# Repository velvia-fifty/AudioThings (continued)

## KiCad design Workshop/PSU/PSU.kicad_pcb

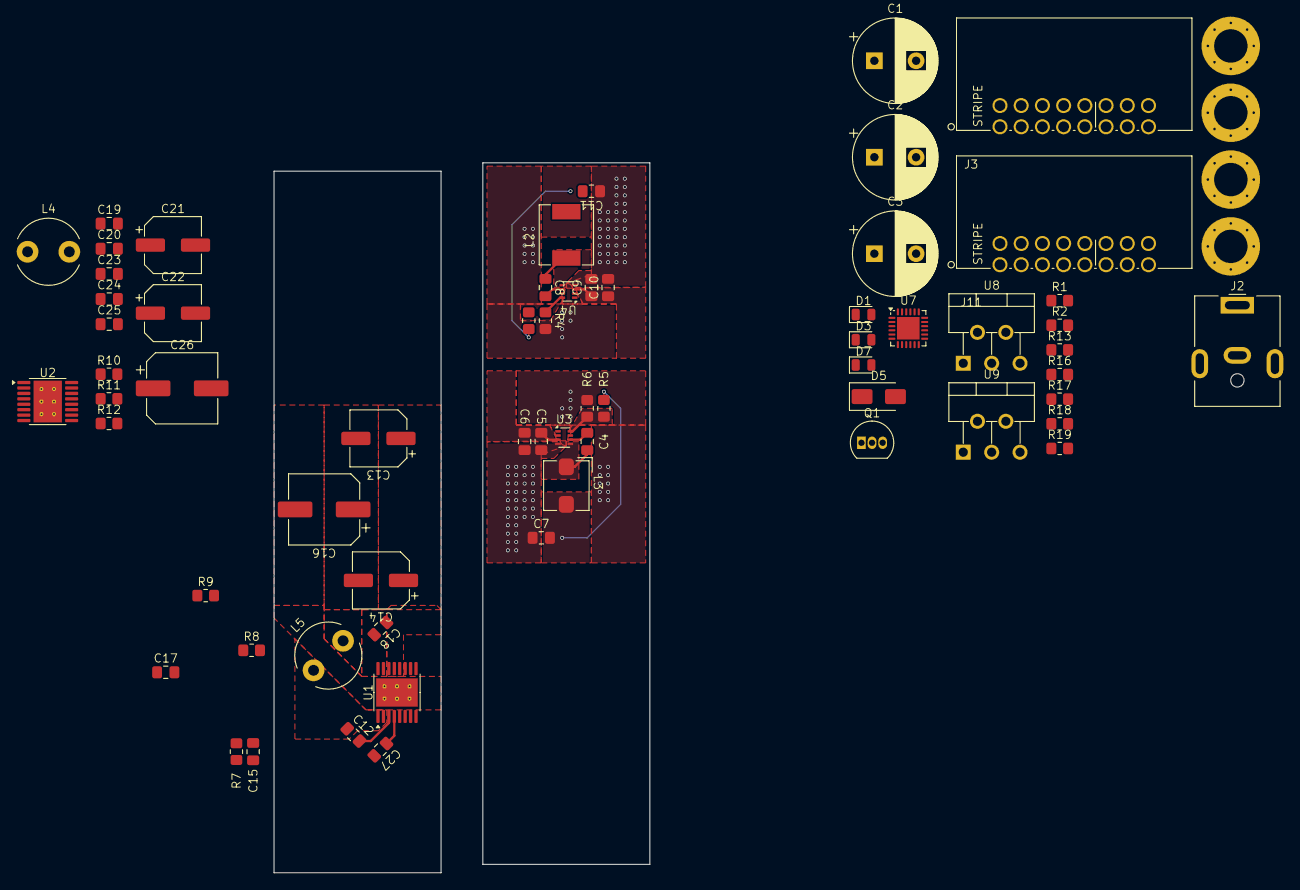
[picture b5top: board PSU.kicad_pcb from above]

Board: 2 copper layers, 45.0 x 85.0 mm, 67 parts (0 on the bottom side), 37 nets.

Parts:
C1, C3: 680uF; CP_Radial_D10.0mm_P5.00mm
C2: 180uF; CP_Radial_D10.0mm_P5.00mm
C4, C6, C8, C10: 100nF; C_0805_2012Metric_Pad1.18x1.45mm_HandSolder
C5, C9: 10uf; C_0805_2012Metric_Pad1.18x1.45mm_HandSolder
C7, C11: 47uf; C_0805_2012Metric_Pad1.18x1.45mm_HandSolder
C12, C23: 680nF; C_0805_2012Metric_Pad1.18x1.45mm_HandSolder
C13, C14, C21, C22: 56uF; CP_Elec_6.3x7.7
C15, C25: 150pF; C_0805_2012Metric_Pad1.18x1.45mm_HandSolder
C16, C26: 100uF; CP_Elec_8x6.9
C17, C18, C20, C24: 4.7uf; C_0805_2012Metric_Pad1.18x1.45mm_HandSolder
C19, C27: 2.2uf; C_0805_2012Metric_Pad1.18x1.45mm_HandSolder
D1: 5V OK; LED_0805_2012Metric
D3: -12V OK; LED_0805_2012Metric
D5: SMAZ18-13-F; D_SMA
D7: 12V OK; LED_0805_2012Metric
H1, H5, H6, H7: H_HOLE; H_ATX_PERF
J2: OPT_DC; BarrelJack_CUI_PJ-063AH_Horizontal
J3, J11: EURO_CONN; EURORACK Right Angle
L2: 5.6uH; IND_SRP6540-5R6M
L3: 4.7uH; L_Bourns_SRP5030T
L4, L5: 56uH; L_Radial_D7.8mm_P5.00mm_Fastron_07HCP
Q1: 2N3904; TO-92_Inline
R1, R2: 500; R_0805_2012Metric_Pad1.20x1.40mm_HandSolder
R3: 52k3; R_0805_2012Metric_Pad1.20x1.40mm_HandSolder
R4, R6, R17, R18: 10k; R_0805_2012Metric_Pad1.20x1.40mm_HandSolder
R5: 140k; R_0805_2012Metric_Pad1.20x1.40mm_HandSolder
R7, R11: 1M; R_0805_2012Metric_Pad1.20x1.40mm_HandSolder
R8, R10: 100k; R_0805_2012Metric_Pad1.20x1.40mm_HandSolder
R9, R12: 92k; R_0805_2012Metric_Pad1.20x1.40mm_HandSolder
R13: 150; R_0805_2012Metric_Pad1.20x1.40mm_HandSolder
R16: 1k; R_0805_2012Metric_Pad1.20x1.40mm_HandSolder
R19: 47k; R_0805_2012Metric_Pad1.20x1.40mm_HandSolder
U1, U2: LM43601PWPR; HTSSOP-16-1EP_4.4x5mm_P0.65mm_EP3.4x5mm_Mask2.46x2.31mm_The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
U3, U4: TPS563300; SOT-583-8
U7: STUSB4500QTR; QFN-24-1EP_4x4mm_P0.5mm_EP2.7x2.7mm
U8, U9: LM2596T-12; TO-220-5_P3.4x3.7mm_StaggerOdd_Lead3.8mm_Vertical

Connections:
+5V: D1.2 (A), J3.11, J3.12, J11.11, J11.12
+5v: C11.2, L2.2, R3.2
+12v: C2.1, C7.2, D7.2 (A), J3.9, J3.10, J11.9, J11.10, L3.2, R5.2, U8.4 (FB)
-12V: C3.2, D3.1 (K), J3.1, J3.2, J11.1, J11.2, Q1.1 (E), R18.1, U9.3 (GND)
-12v B: C16.2, C17.2, C18.2, C27.2, R9.2, U1.10 (AGND), U1.15 (PGND), U1.16 (PGND)
/5v FB: R3.1, R4.1, U4.8 (FB)
/5v SW: C8.1, L2.1, U4.5 (SW)
/12v FB: R5.1, R6.1, U3.8 (FB)
/12v SW: C4.1, L3.1, U3.5 (SW)
/+20V: C1.1, J2.1, U7.16 (VBUS_EN_SNK), U8.1 (VIN)
/-12v B Bias: C15.2, R7.2, R9.1, U1.9 (FB)
/-12v B CBOOT: C12.1, L5.1, U1.1 (SW), U1.2 (SW)
/CC1: U7.1 (CC1DB), U7.2 (CC1)
/CC2: U7.4 (CC2), U7.5 (CC2DB)
/CV: J3.13, J3.14, J11.13, J11.14
/GATE: J3.15, J3.16, J11.15, J11.16
/VBUS: R16.2, U7.24 (VDD)
COM: C1.2, C2.2, C5.2, C6.2, C7.1, C9.2, C10.2, C11.1, C13.2, C14.2, C15.1, C16.1, C17.1, C19.2, C20.2, C21.2, C22.2, C24.1, C24.2, C25.1, C25.2, C26.1, C26.2, H1.1, H5.1, H6.1, H7.1, J2.2, J3.3, J3.4, J3.5, J3.6, J3.7, J3.8, J11.3, J11.4, J11.5, J11.6, J11.7, J11.8, L4.2, L5.2, R1.1, R2.2, R4.2, R6.2, R7.1, R8.1, R10.1, R11.1, R11.2, R12.1, R12.2, U1.5 (BIAS), U2.5 (BIAS), U2.10 (AGND), U2.15 (PGND), U2.16 (PGND), U3.4 (GND), U4.4 (GND), U8.3 (GND), U8.5 (~ON/OFF)
unnamed: C23.1, L4.1, U2.1 (SW), U2.2 (SW)
unnamed: D1.1 (K), R13.2
unnamed: D3.2 (A), R2.1
unnamed: C3.1, R17.2, R19.2, U9.1 (VIN)
unnamed: D5.2 (A), Q1.2 (B), R18.2
unnamed: D5.1 (K), R17.1
unnamed: D7.1 (K), R1.2
unnamed: Q1.3 (C), R19.1, U9.5 (~ON/OFF)
unnamed: C12.2, U1.3 (CBOOT)
unnamed: R8.2, U1.8 (PGOOD)
unnamed: C27.1, U1.4 (VCC)
unnamed: C23.2, U2.3 (CBOOT)
unnamed: R10.2, U2.8 (PGOOD)
unnamed: C19.1, U2.4 (VCC)
unnamed: C4.2, U3.6 (BST)
unnamed: C8.2, U4.6 (BST)
unnamed: U7.10 (GND), U7.25 (GND)
unnamed: R16.1, U7.18 (VBUS_VS_DISCH)
PD +15v: C5.1, C6.1, C9.1, C10.1, C13.1, C14.1, C18.1, C20.1, C21.1, C22.1, U1.12 (EN), U1.13 (VIN), U1.14 (VIN), U2.12 (EN), U2.13 (VIN), U2.14 (VIN), U3.3 (VIN), U4.3 (VIN)

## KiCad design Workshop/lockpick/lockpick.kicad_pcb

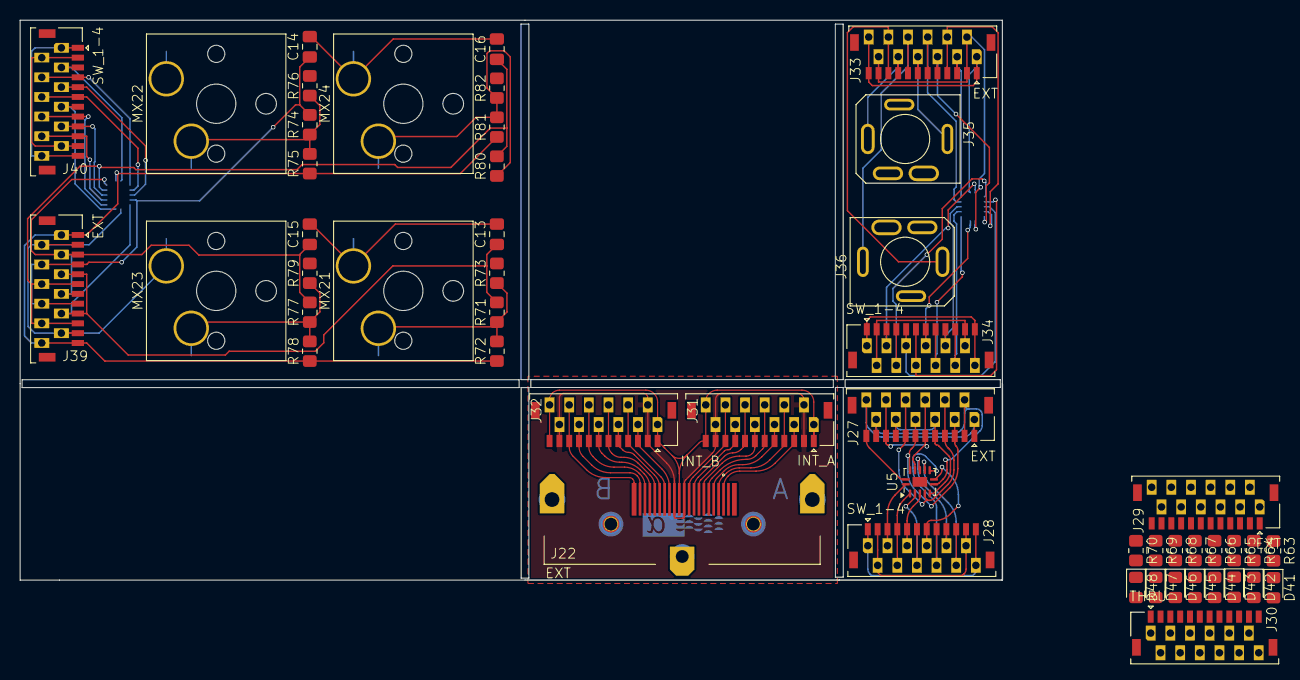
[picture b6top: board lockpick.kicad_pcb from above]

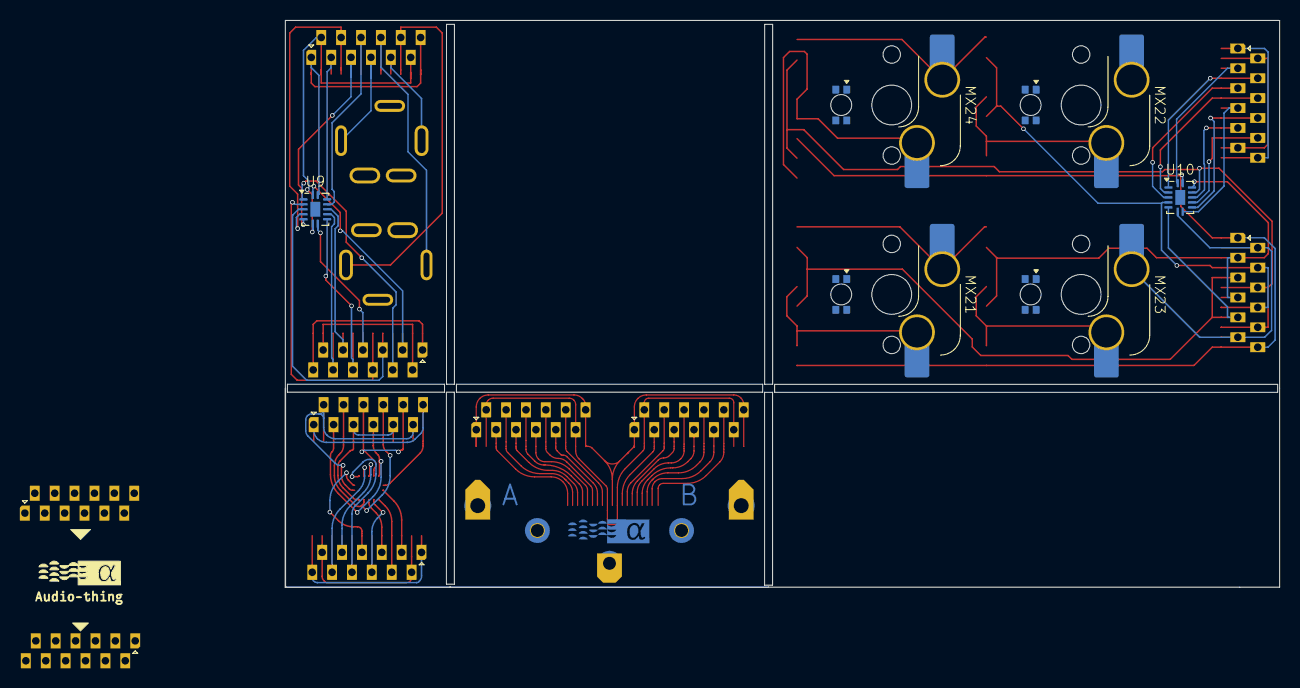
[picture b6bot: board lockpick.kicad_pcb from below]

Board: 2 copper layers, 100.0 x 57.0 mm, 53 parts (3 on the bottom side), 92 nets.

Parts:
***: at-logo-cu
C13, C14, C15, C16: 1uF; C_0805_2012Metric_Pad1.18x1.45mm_HandSolder
D41: ACT_1; LED_0805_2012Metric_Pad1.15x1.40mm_HandSolder
D42: ACT_2; LED_0805_2012Metric_Pad1.15x1.40mm_HandSolder
D43: ACT_3; LED_0805_2012Metric_Pad1.15x1.40mm_HandSolder
D44: ACT_4; LED_0805_2012Metric_Pad1.15x1.40mm_HandSolder
D45: ACT_5; LED_0805_2012Metric_Pad1.15x1.40mm_HandSolder
D46: ACT_6; LED_0805_2012Metric_Pad1.15x1.40mm_HandSolder
D47: ACT_7; LED_0805_2012Metric_Pad1.15x1.40mm_HandSolder
D48: ACT_8; LED_0805_2012Metric_Pad1.15x1.40mm_HandSolder
J22: EXT; AMPHENOL_10078837-001LF
J27, J29, J33, J39: EXT; JST_SHL 12pin w pads
J28, J34, J40: SW_1-4; JST_SHL 12pin w pads
J30: THRU; JST_SHL 12pin w pads
J31: INT_A; JST_SHL 12pin w pads
J32: INT_B; JST_SHL 12pin w pads
J35: MONO 1; SJ3-3505
J36: MONO 2; SJ3-3505
MX21: Trigger 3; SW_Hotswap_Kailh_MX_Plated_1206R LED
MX22: Trigger 2; SW_Hotswap_Kailh_MX_Plated_1206R LED
MX23: Trigger 1; SW_Hotswap_Kailh_MX_Plated_1206R LED
MX24: Trigger 4; SW_Hotswap_Kailh_MX_Plated_1206R LED
R63, R64, R65, R66, R67, R68, R69, R70, R73, R76, R79, R82: 150R; R_0805_2012Metric_Pad1.20x1.40mm_HandSolder
R71, R74, R77, R80: 1k; R_0805_2012Metric_Pad1.20x1.40mm_HandSolder
R72, R75, R78, R81: 10k; R_0805_2012Metric_Pad1.20x1.40mm_HandSolder
U5, U9, U10: 4066; DHVQFN-14-1EP_2.5x3mm_P0.5mm_EP1x1.5mm

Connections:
/Device Modules/4 to ARB + 2 Stereo/DEV_GND: J34.2, J34.11
/Device Modules/4 to ARB + 2 Stereo/DEV_PWR: J34.1, J34.12
/Device Modules/4 to ARB + 2 Stereo/EXT_GND: J33.2, J33.11, U9.7 (VSS)
/Device Modules/4 to ARB + 2 Stereo/EXT_PWR: J33.1, J33.12, U9.14 (VDD)
/Device Modules/4 to ARB + 2 Stereo/MONO_1: J33.7, J35.T
/Device Modules/4 to ARB + 2 Stereo/MONO_2: J33.8, J36.T
/Device Modules/4 to ARB + 2 Stereo/MONO_3: J33.9, J35.R
/Device Modules/4 to ARB + 2 Stereo/MONO_4: J33.10, J36.R
/Device Modules/4 to ARB + 2 Stereo/SW_1: J34.3, U9.1
/Device Modules/4 to ARB + 2 Stereo/SW_2: J34.5, U9.4
/Device Modules/4 to ARB + 2 Stereo/SW_3: J34.7, U9.8
/Device Modules/4 to ARB + 2 Stereo/SW_4: J34.9, U9.11
/Device Modules/4 to ARB + 2 Stereo/SW_B1: J34.4, U9.2
/Device Modules/4 to ARB + 2 Stereo/SW_B2: J34.6, U9.3
/Device Modules/4 to ARB + 2 Stereo/SW_B3: J34.8, U9.9
/Device Modules/4 to ARB + 2 Stereo/SW_B4: J34.10, U9.10
/Device Modules/4 to ARB + 2 Stereo/TRIG_1: J33.3, U9.13
/Device Modules/4 to ARB + 2 Stereo/TRIG_2: J33.4, U9.5
/Device Modules/4 to ARB + 2 Stereo/TRIG_3: J33.5, U9.6
/Device Modules/4 to ARB + 2 Stereo/TRIG_4: J33.6, U9.12
/Device Modules/4 to ARB + Keys/DEV_GND: J40.2, J40.11
/Device Modules/4 to ARB + Keys/DEV_PWR: J40.1, J40.12
/Device Modules/4 to ARB + Keys/EXT_GND: C13.2, C14.2, C15.2, C16.2, J39.2, J39.11, MX21.2, MX21.L1, MX22.2, MX22.L1, MX23.2, MX23.L1, MX24.2, MX24.L1, U10.7 (VSS)
/Device Modules/4 to ARB + Keys/EXT_PWR: J39.1, J39.12, R72.1, R75.1, R78.1, R81.1, U10.14 (VDD)
/Device Modules/4 to ARB + Keys/SW_1: J40.3, U10.1
/Device Modules/4 to ARB + Keys/SW_2: J40.5, U10.4
/Device Modules/4 to ARB + Keys/SW_3: J40.7, U10.8
/Device Modules/4 to ARB + Keys/SW_4: J40.9, U10.11
/Device Modules/4 to ARB + Keys/SW_B1: J40.4, U10.2
/Device Modules/4 to ARB + Keys/SW_B2: J40.6, U10.3
/Device Modules/4 to ARB + Keys/SW_B3: J40.8, U10.9
/Device Modules/4 to ARB + Keys/SW_B4: J40.10, U10.10
/Device Modules/4 to ARB + Keys/TRIG_1: C15.1, J39.3, J39.7, R77.2, U10.13
/Device Modules/4 to ARB + Keys/TRIG_2: C14.1, J39.4, J39.8, R74.2, U10.5
/Device Modules/4 to ARB + Keys/TRIG_3: C13.1, J39.5, J39.9, R71.2, U10.6
/Device Modules/4 to ARB + Keys/TRIG_4: C16.1, J39.6, J39.10, R80.2, U10.12
/Device Modules/4 to ARB/DEV_GND: J28.2, J28.11
/Device Modules/4 to ARB/DEV_PWR: J28.1, J28.12
/Device Modules/4 to ARB/EXT_GND: J27.2, J27.11, U5.7 (VSS)
/Device Modules/4 to ARB/EXT_PWR: J27.1, J27.12, U5.14 (VDD)
/Device Modules/4 to ARB/SW_1: J28.3, U5.1
/Device Modules/4 to ARB/SW_2: J28.5, U5.4
/Device Modules/4 to ARB/SW_3: J28.7, U5.8
/Device Modules/4 to ARB/SW_4: J28.9, U5.11
/Device Modules/4 to ARB/SW_B1: J28.4, U5.2
/Device Modules/4 to ARB/SW_B2: J28.6, U5.3
/Device Modules/4 to ARB/SW_B3: J28.8, U5.9
/Device Modules/4 to ARB/SW_B4: J28.10, U5.10
/Device Modules/4 to ARB/TRIG_1: J27.3, J27.7, U5.13
/Device Modules/4 to ARB/TRIG_2: J27.4, J27.8, U5.5
/Device Modules/4 to ARB/TRIG_3: J27.5, J27.9, U5.6
/Device Modules/4 to ARB/TRIG_4: J27.6, J27.10, U5.12
/Indicator/EXT_GND: J29.2, J29.11, J30.2, J30.11, R63.1, R64.1, R65.1, R66.1, R67.1, R68.1, R69.1, R70.1
/Indicator/EXT_PWR: J29.1, J29.12, J30.1, J30.12
/Indicator/THRU_1: D41.2 (A), J29.3, J30.3
/Indicator/THRU_2: D42.2 (A), J29.4, J30.4
/Indicator/THRU_3: D43.2 (A), J29.5, J30.5
/Indicator/THRU_4: D44.2 (A), J29.6, J30.6
/Indicator/THRU_5: D45.2 (A), J29.7, J30.7
/Indicator/THRU_6: D46.2 (A), J29.8, J30.8
/Indicator/THRU_7: D47.2 (A), J29.9, J30.9
/Indicator/THRU_8: D48.2 (A), J29.10, J30.10
/Passthru/EXT_GND: J22.9, J22.11, J31.2, J31.11, J32.2, J32.11
/Passthru/EXT_PWR: J22.10, J31.1, J31.12, J32.1, J32.12
/Passthru/TRIGGER 1: J22.1, J31.3
/Passthru/TRIGGER 2: J22.2, J31.4
/Passthru/TRIGGER 3: J22.3, J31.5
/Passthru/TRIGGER 4: J22.4, J31.6
/Passthru/TRIGGER 5: J22.5, J31.7
/Passthru/TRIGGER 6: J22.6, J31.8
/Passthru/TRIGGER 7: J22.7, J31.9
/Passthru/TRIGGER 8: J22.8, J31.10
/Passthru/TRIGGER 9: J22.12, J32.3
/Passthru/TRIGGER 10: J22.13, J32.4
/Passthru/TRIGGER 11: J22.14, J32.5
/Passthru/TRIGGER 12: J22.15, J32.6
/Passthru/TRIGGER 13: J22.16, J32.7
/Passthru/TRIGGER 14: J22.17, J32.8
/Passthru/TRIGGER 15: J22.18, J32.9
/Passthru/TRIGGER 16: J22.19, J32.10
unnamed: D41.1 (K), R63.2
unnamed: D42.1 (K), R64.2
unnamed: D43.1 (K), R65.2
unnamed: D44.1 (K), R66.2
unnamed: D45.1 (K), R67.2
unnamed: D46.1 (K), R68.2
unnamed: D47.1 (K), R69.2
unnamed: D48.1 (K), R70.2
unnamed: MX21.1, R71.1, R72.2, R73.1
unnamed: MX22.1, R74.1, R75.2, R76.1
unnamed: MX23.1, R77.1, R78.2, R79.1
unnamed: MX24.1, R80.1, R81.2, R82.1

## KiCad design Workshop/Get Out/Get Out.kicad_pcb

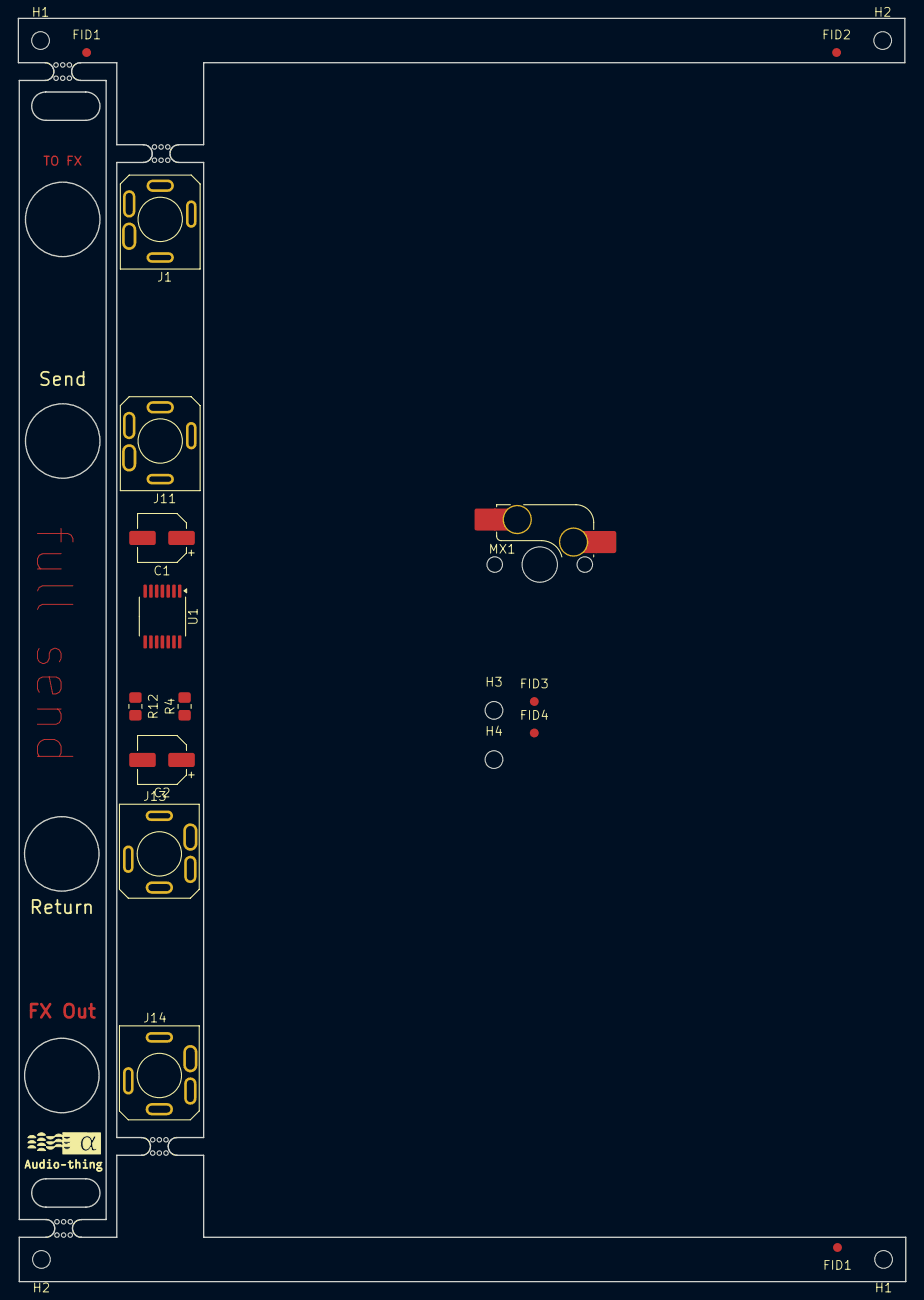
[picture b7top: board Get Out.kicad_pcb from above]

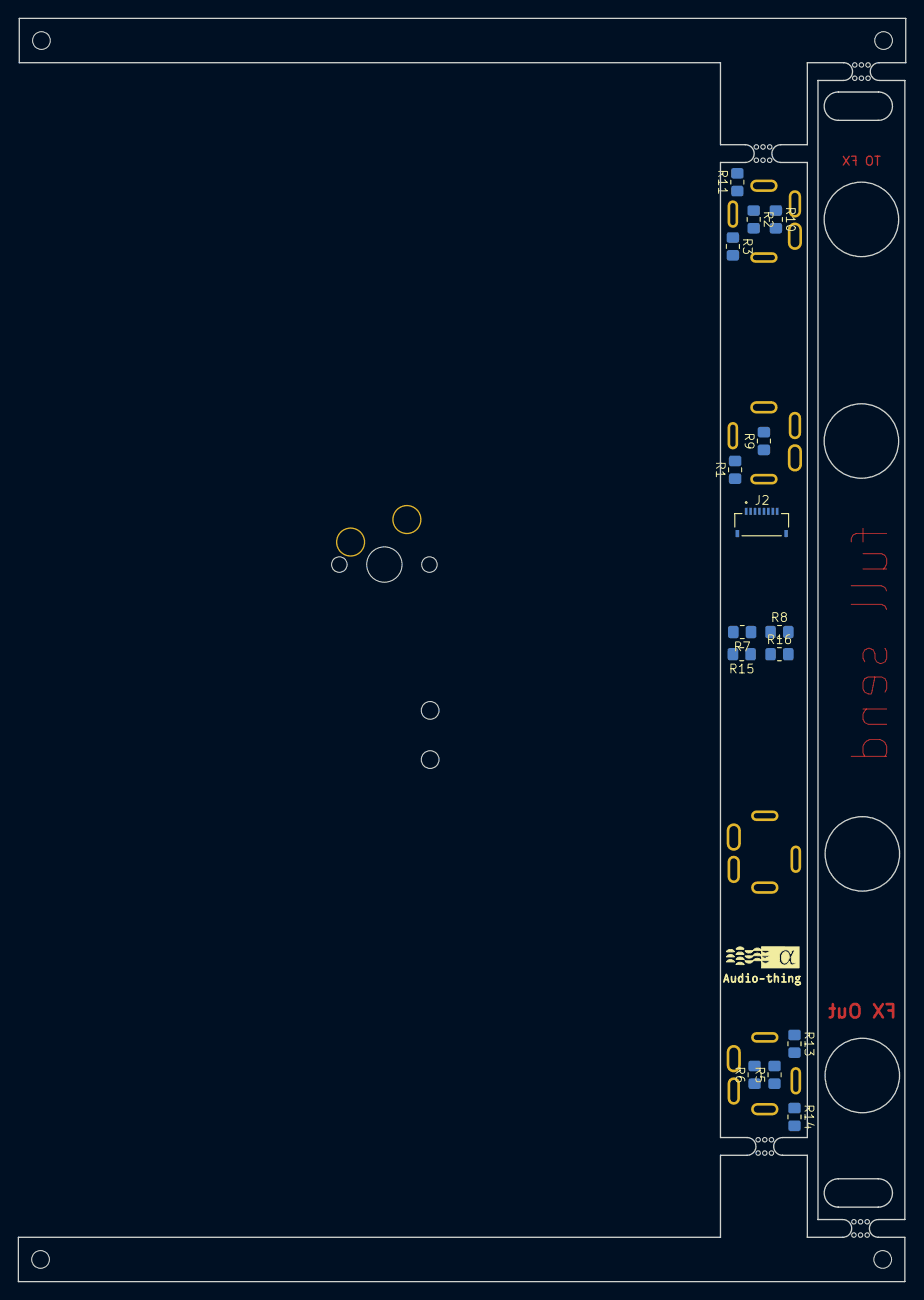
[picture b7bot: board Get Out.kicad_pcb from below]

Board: 2 copper layers, 100.1 x 142.5 mm, 40 parts (15 on the bottom side), 21 nets, no tracks yet.

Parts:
C1, C2: 10uF; CP_Elec_5x5.4
FID1, FID1#2, FID2, FID3, FID4: Fiducial; Fiducial_1mm_Mask2mm
H1, H1#2, H2, H2#2, H3, H4: Tooling; MountingHole_2mm
J1: TO FX; SJ3-3505
J2: FFFPWR; AMPHENOL_F33B-1A7Q1-E8C08
J11: FX SEND; SJ3-3505
J13: FX RETURN; SJ3-3505
J14: FROM FX; SJ3-3505
MX1: MX_SW_HS; SW_MX_HS_CPG151101S11_1u
R1, R3, R6, R9, R11, R14: 1k; R_0805_2012Metric_Pad1.20x1.40mm_HandSolder
R2, R10: 20k; R_0805_2012Metric_Pad1.20x1.40mm_HandSolder
R4, R12: 470R; R_0805_2012Metric_Pad1.20x1.40mm_HandSolder
R5, R13: 10k; R_0805_2012Metric_Pad1.20x1.40mm_HandSolder
R7, R15: 1M; R_0805_2012Metric_Pad1.20x1.40mm_HandSolder
R8, R16: 150k; R_0805_2012Metric_Pad1.20x1.40mm_HandSolder
U1: TL074; TSSOP-14_4.4x5mm_P0.65mm
mouse-bite-2mm-slot, mouse-bite-2mm-slot#2, mouse-bite-2mm-slot#3, mouse-bite-2mm-slot#4: VAL**; mouse-bite-2mm-slot

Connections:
/Output/+12v: J2.2, J2.3
/Output/-12v: J2.6, J2.7
/Output/DRY L: J11.T, R1.2
/Output/DRY R: J11.R, R9.2
/Output/WET L: J14.T, R6.2
/Output/WET R: J14.R, R14.2
GND: J1.S, J2.1, J2.4, J2.5, J2.8, J11.S, J13.S, J14.S, R3.1, R4.1, R7.1, R8.1, R11.1, R12.1, R15.1, R16.1
unnamed: C1.1, J13.T, R7.2
unnamed: C2.1, J13.R, R15.2
unnamed: J1.R, R10.1
unnamed: J1.T, R2.1
unnamed: R5.2, R6.1, U1.8
unnamed: R13.2, R14.1, U1.14
unnamed: R2.2, R3.2, U1.3 (+)
unnamed: R1.1, U1.1, U1.2 (-)
unnamed: R10.2, R11.2, U1.5 (+)
unnamed: R9.1, U1.6 (-), U1.7
unnamed: C1.2, R8.2, U1.10 (+)
unnamed: R4.2, R5.1, U1.9 (-)
unnamed: C2.2, R16.2, U1.12 (+)
unnamed: R12.2, R13.1, U1.13 (-)

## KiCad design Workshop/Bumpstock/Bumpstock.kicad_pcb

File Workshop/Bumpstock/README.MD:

The Intel i487 Math Co-processor is just a 486, that's it, if you didn't get the good 486 now you're buying two just to suck less at Quake.

Anyway, I built a clock divider and accidentally a sequencer while I was procrastinating

Q: This is three modules...
A: In a trenchcoat, don't forget the trenchcoat...

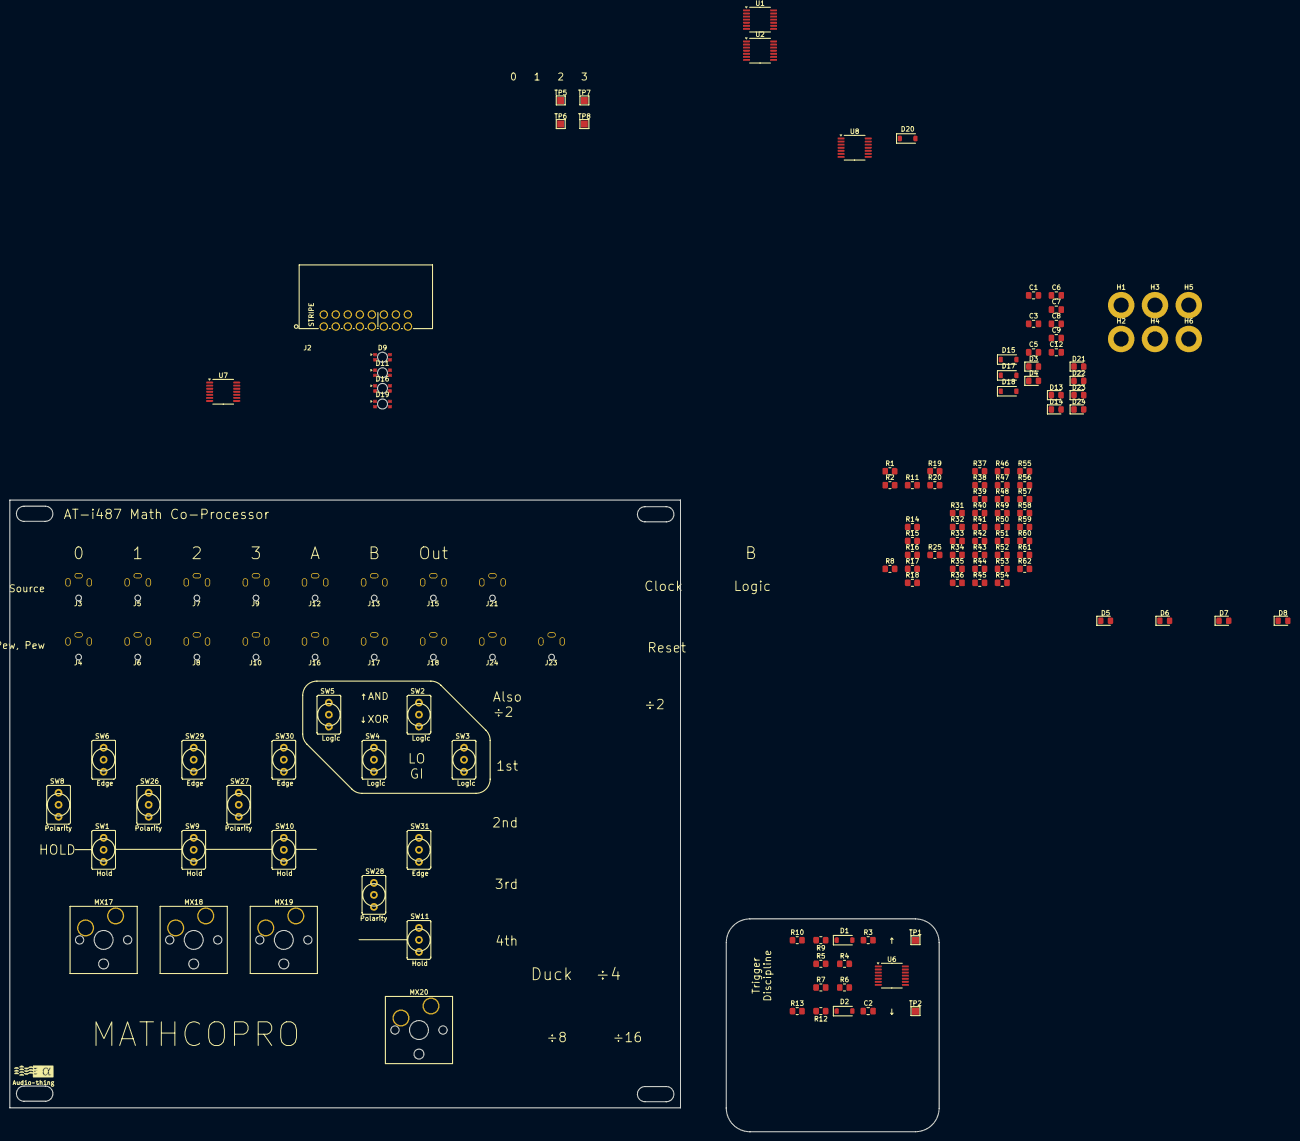
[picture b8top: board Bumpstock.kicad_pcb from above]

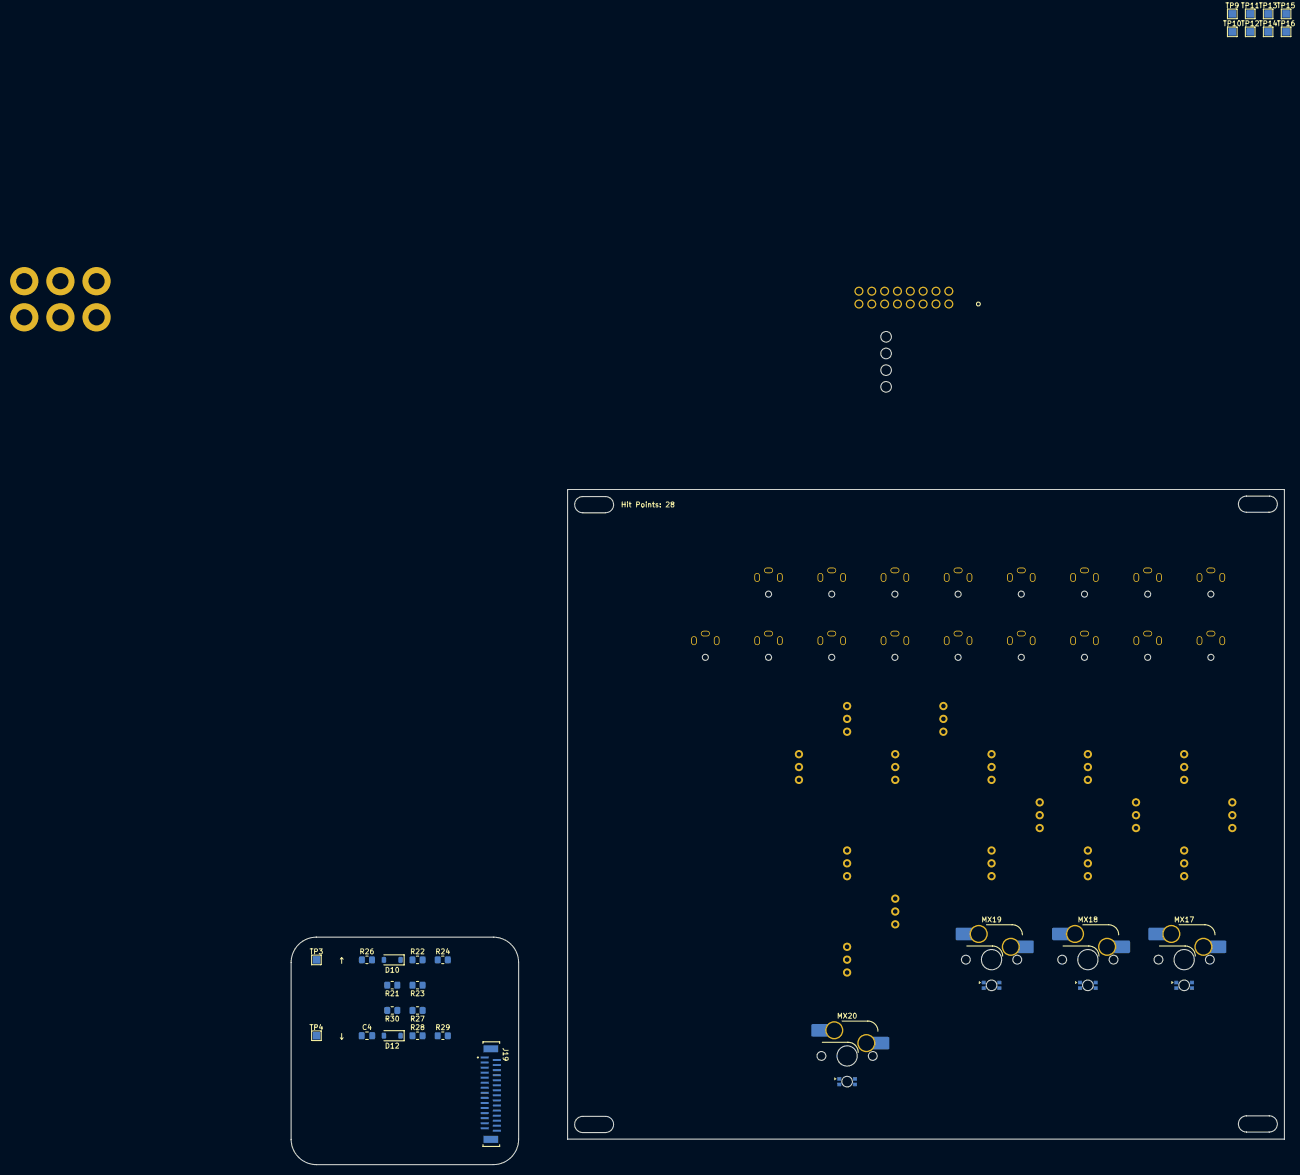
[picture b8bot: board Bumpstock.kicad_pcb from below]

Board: 2 copper layers, 196.5 x 133.6 mm, 162 parts (23 on the bottom side), 98 nets, no tracks yet.

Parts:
C1, C3, C5, C7: 1uF; C_0805_2012Metric_Pad1.18x1.45mm_HandSolder
C2, C4, C6, C8, C9, C12: 10nf; C_0805_2012Metric_Pad1.18x1.45mm_HandSolder
D1, D2, D10, D12, D15, D17, D18, D20: 1N4148W; D_SOD-123
D3, D13, D21, D23: Rise; LED_0805_2012Metric_Pad1.15x1.40mm_HandSolder
D4, D14, D22, D24: Fall; LED_0805_2012Metric_Pad1.15x1.40mm_HandSolder
D5: Out 0; LED_0805_2012Metric_Pad1.15x1.40mm_HandSolder
D6, D7, D8: Out; LED_0805_2012Metric_Pad1.15x1.40mm_HandSolder
D9: Out MX 0; LED_MX_1206R
D11: Out MX 1; LED_MX_1206R
D16: Out MX 2; LED_MX_1206R
D19: Out MX 3; LED_MX_1206R
H1, H2, H3, H4, H5, H6: M3; MountingHole_3.2mm_M3_DIN965_Pad
J2: OPT EURO; EURORACK Right Angle
J3: In 0; SJ3
J4: Out 0; SJ3
J5: In 1; SJ3
J6: Out 1; SJ3
J7: In 2; SJ3
J8: Out 2; SJ3
J9: In 3; SJ3
J10: Out 3; SJ3
J12: Logic 0 A; SJ3
J13: Logic 0 B; SJ3
J15: Logic 0 Out; SJ3
J16: Logic 1 A; SJ3
J17: Logic 1 B; SJ3
J18: Logic 1 Out; SJ3
J19: EXT; ffc-30-v-TE_3-1734742-0
J21: Logic 2 Out; SJ3
J23: Logic X; SJ3
J24: Logic 3 Out; SJ3
MX17: Trigger 0; SW_Hotswap_Kailh_MX_Plated_1206R LED
MX18: Trigger 1; SW_Hotswap_Kailh_MX_Plated_1206R LED
MX19: Trigger 2; SW_Hotswap_Kailh_MX_Plated_1206R LED
MX20: Trigger 3; SW_Hotswap_Kailh_MX_Plated_1206R LED
R1, R5, R7, R19, R23, R27, R33, R37, R41, R45, R49, R53: 1k; R_0805_2012Metric_Pad1.20x1.40mm_HandSolder
R2, R20, R34, R46: 10k; R_0805_2012Metric_Pad1.20x1.40mm_HandSolder
R3, R4, R6, R21, R26, R30, R35, R40, R44, R47, R52, R56: 100k; R_0805_2012Metric_Pad1.20x1.40mm_HandSolder
R8, R11, R31, R32, R59, R60, R61, R62: 500R; R_0805_2012Metric_Pad1.20x1.40mm_HandSolder
R9, R12, R22, R28, R36, R42, R48, R54: 2.7k; R_0805_2012Metric_Pad1.20x1.40mm_HandSolder
R10, R13, R24, R29, R38, R43, R50, R55: 2.2k; R_0805_2012Metric_Pad1.20x1.40mm_HandSolder
R14, R15, R16, R17, R18, R25, R39, R51: 150R; R_0805_2012Metric_Pad1.20x1.40mm_HandSolder
R57, R58: 10R; R_0805_2012Metric_Pad1.20x1.40mm_HandSolder
SW1, SW9, SW10, SW11: Hold; Switch_Toggle_SPDT_SubMini
SW2, SW3, SW4, SW5: Logic; Switch_Toggle_SPDT_SubMini
SW6, SW29, SW30, SW31: Edge; Switch_Toggle_SPDT_SubMini
SW8, SW26, SW27, SW28: Polarity; Switch_Toggle_SPDT_SubMini
TP1: Rising 0; TestPoint_Pad_1.5x1.5mm
TP2: Falling 0; TestPoint_Pad_1.5x1.5mm
TP3: Rising 1; TestPoint_Pad_1.5x1.5mm
TP4: Falling 1; TestPoint_Pad_1.5x1.5mm
TP5: Rising 2; TestPoint_Pad_1.5x1.5mm
TP6: Falling 2; TestPoint_Pad_1.5x1.5mm
TP7: Rising 3; TestPoint_Pad_1.5x1.5mm
TP8: Falling 3; TestPoint_Pad_1.5x1.5mm
TP9: AND 2; TestPoint_Pad_1.5x1.5mm
TP10: XOR 2; TestPoint_Pad_1.5x1.5mm
TP11: AND 3; TestPoint_Pad_1.5x1.5mm
TP12: XOR 3; TestPoint_Pad_1.5x1.5mm
TP13: AND 1; TestPoint_Pad_1.5x1.5mm
TP14: XOR 1; TestPoint_Pad_1.5x1.5mm
TP15: AND 0; TestPoint_Pad_1.5x1.5mm
TP16: XOR 0; TestPoint_Pad_1.5x1.5mm
U1: 74LS08; TSSOP-14_4.4x5mm_P0.65mm
U2: 74LS86; TSSOP-14_4.4x5mm_P0.65mm
U6, U8: TL074; TSSOP-14_4.4x5mm_P0.65mm
U7: 40106; TSSOP-14_4.4x5mm_P0.65mm

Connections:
+5V: J2.11, J2.12, J19.1, J19.30, R2.1, R20.1, R34.1, R46.1
+12V: C9.2, J2.9, J2.10, R57.1, R57.2, U6.4 (V+), U8.4 (V+)
+12v: R4.2, R21.2, R35.2, R47.2
-12V: J2.1, J2.2, R58.1
-12v: C12.1, R6.2, R30.2, R44.2, R56.2, R58.2, U6.11 (V-), U8.11 (V-)
/Bus/CON_CV: J2.13, J2.14
/Bus/CON_GATE: J2.15, J2.16
Fall 0: J19.11, R12.2, R13.2, SW6.3 (C), TP2.1
Fall 1: J19.23, R28.2, R29.2, SW29.3 (C), TP4.1
Fall 2: R42.2, R43.2, SW30.3 (C), TP6.1
Fall 3: R54.2, R55.2, SW31.3 (C), TP8.1
GND: C1.2, C3.2, C5.2, C7.2, C9.1, C12.2, D3.1 (K), D4.1 (K), D5.1 (K), D6.1 (K), D7.1 (K), D8.1 (K), D9.1 (K), D11.1 (K), D13.1 (K), D14.1 (K), D16.1 (K), D19.1 (K), D21.1 (K), D22.1 (K), D23.1 (K), D24.1 (K), J2.3, J2.4, J2.5, J2.6, J2.7, J2.8, J3.S, J4.S, J5.S, J6.S, J7.S, J8.S, J9.S, J10.S, J12.S, J13.S, J15.S, J16.S, J17.S, J18.S, J19.2, J19.4, J19.6, J19.8, J19.10, J19.12, J19.14, J19.16, J19.18, J19.20, J19.22, J19.24, J19.26, J19.29, J19.S1, J21.S, J23.S, J24.S, MX17.2, MX18.2, MX19.2, MX20.2, R3.1, R5.1, R7.1, R10.1, R13.1, R23.1, R24.1, R26.1, R27.1, R29.1, R37.1, R38.1, R40.1, R41.1, R43.1, R49.1, R50.1, R52.1, R53.1, R55.1, SW1.2 (B), SW9.2 (B), SW10.2 (B), SW11.2 (B)
IN 0: C1.1, C2.1, J3.T, J19.13, R1.2
IN 1: C3.1, C4.1, J5.T, J19.25, R19.2
IN 2: C5.1, C6.1, J7.T, R33.2
IN 3: C7.1, C8.1, J9.T, R45.2
LED FALL 0: D2.1 (K), J19.7, R11.2, R12.1
LED FALL 1: D12.1 (K), J19.19, R28.1, R32.2
LED FALL 2: D17.1 (K), R42.1, R60.2
LED FALL 3: D20.1 (K), R54.1, R62.2
LED RISE 0: D1.1 (K), J19.3, R8.2, R9.1
LED RISE 1: D10.1 (K), J19.15, R22.1, R31.2
LED RISE 2: D15.1 (K), R36.1, R59.2
LED RISE 3: D18.1 (K), R48.1, R61.2
Logic 0 A: J12.T, U1.1, U2.1
Logic 0 B: J13.T, U1.2, U2.2
Logic 0 Out: J15.T, SW5.2 (B), U1.9, U2.9
Logic 1 A: J16.T, U1.4, U2.4
Logic 1 B: J17.T, U1.5, U2.5
Logic 1 Out: J18.T, SW4.2 (B), U1.10, U2.10
Logic 2 Out: J21.T, SW2.2 (B), U1.12, U2.12
Logic 3 Out: J24.T, SW3.2 (B)
Logic X: J23.T, U1.13, U2.13
MX LED 0 +: J4.T, J19.5, R14.2, R18.2, SW8.2 (B)
MX LED 1 +: J19.17, R25.2
unnamed: D1.2 (A), U6.1
unnamed: D2.2 (A), U6.7
unnamed: D3.2 (A), R8.1
unnamed: D4.2 (A), R11.1
unnamed: D5.2 (A), R14.1
unnamed: D6.2 (A), R15.1
unnamed: D7.2 (A), R16.1
unnamed: D8.2 (A), R17.1
unnamed: D9.2 (A), R18.1
unnamed: D10.2 (A), U6.8
unnamed: D11.2 (A), R25.1
unnamed: D12.2 (A), U6.14
unnamed: D13.2 (A), R31.1
unnamed: D14.2 (A), R32.1
unnamed: D15.2 (A), U8.1
unnamed: D16.2 (A), R39.1
unnamed: D17.2 (A), U8.7
unnamed: D18.2 (A), U8.8
unnamed: D19.2 (A), R51.1
unnamed: D20.2 (A), U8.14
unnamed: D21.2 (A), R59.1
unnamed: D22.2 (A), R60.1
unnamed: D23.2 (A), R61.1
unnamed: D24.2 (A), R62.1
unnamed: MX17.1, R1.1, R2.2, SW1.1 (A)
unnamed: SW2.1 (A), TP9.1, U1.8
unnamed: SW2.3 (C), TP10.1, U2.8
unnamed: SW3.1 (A), TP11.1, U1.11
unnamed: SW3.3 (C), TP12.1, U2.11
unnamed: SW4.1 (A), TP13.1, U1.6
unnamed: SW4.3 (C), TP14.1, U2.6
unnamed: SW5.1 (A), TP15.1, U1.3
unnamed: SW5.3 (C), TP16.1, U2.3
unnamed: SW6.2 (B), SW8.1 (A), U7.1
unnamed: SW8.3 (C), U7.2
unnamed: MX18.1, R19.1, R20.2, SW9.1 (A)
unnamed: MX19.1, R33.1, R34.2, SW10.1 (A)
unnamed: MX20.1, R45.1, R46.2, SW11.1 (A)
unnamed: SW26.1 (A), SW29.2 (B), U7.3
unnamed: SW26.3 (C), U7.4
unnamed: SW27.1 (A), SW30.2 (B), U7.5
unnamed: SW27.3 (C), U7.6
unnamed: SW28.1 (A), SW31.2 (B), U7.9
unnamed: SW28.3 (C), U7.8
unnamed: C2.2, R3.2, U6.3 (+), U6.6 (-)
unnamed: R4.1, R5.2, U6.2 (-)
unnamed: R6.1, R7.2, U6.5 (+)
unnamed: C4.2, R26.2, U6.10 (+), U6.13 (-)
unnamed: R21.1, R23.2, U6.9 (-)
unnamed: R27.2, R30.1, U6.12 (+)
unnamed: C6.2, R40.2, U8.3 (+), U8.6 (-)
unnamed: R35.1, R37.2, U8.2 (-)
unnamed: R41.2, R44.1, U8.5 (+)
unnamed: C8.2, R52.2, U8.10 (+), U8.13 (-)
unnamed: R47.1, R49.2, U8.9 (-)
unnamed: R53.2, R56.1, U8.12 (+)
Out 1: J6.T, SW26.2 (B)
Out 2: J8.T, SW27.2 (B)
Out 3: J10.T, SW28.2 (B)
Rise 0: J19.9, R9.2, R10.2, SW6.1 (A), TP1.1
Rise 1: J19.21, R22.2, R24.2, SW29.1 (A), TP3.1
Rise 2: R36.2, R38.2, SW30.1 (A), TP5.1
Rise 3: R48.2, R50.2, SW31.1 (A), TP7.1

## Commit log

2024-10-30 init get it in github nao!
2024-10-30 GET IT IN GITHUB NAO!
2024-10-30 GET IT ON GITHUB NAO!
2024-11-16 ONE-8-DM5 Setup
2024-11-16 RTFM
2024-11-16 LICENSE.MD
2024-11-16 I'm using this wrong and that's OK
2024-11-16 thing
2024-11-16 i did a thing
2024-11-16 did more things
2024-11-16 doot
2024-11-16 how does .gitignore
2024-11-16 remove DS_Store
2024-11-16 things
2024-11-16 better .gitignore jacked from https://www.jcchouinard.com/gitignore-template/
2024-11-16 Stop going to the store
2024-11-16 medical advice
2024-11-16 Standardizing Template, Figuring out Pages
2024-11-16 AudioThings
2024-11-16 increased sexual tension
2024-11-16 did a thing
2024-11-16 yeahmehl
2024-11-16 fuuuuuuuh
2024-11-16 hide
2024-11-16 deindex
2024-11-16 dink
2024-11-16 donk
2024-11-16 dunk
2024-12-07 big old push of morphine to commit war crimes
2024-12-07 P'd the D'd you F
2024-12-11 polished and PSU, did a todo, much ado about something
